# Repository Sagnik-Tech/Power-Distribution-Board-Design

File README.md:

Custom design of a Power Distribution Board from scratch which can provide different voltages required by the various subsystems of a Mars Rover

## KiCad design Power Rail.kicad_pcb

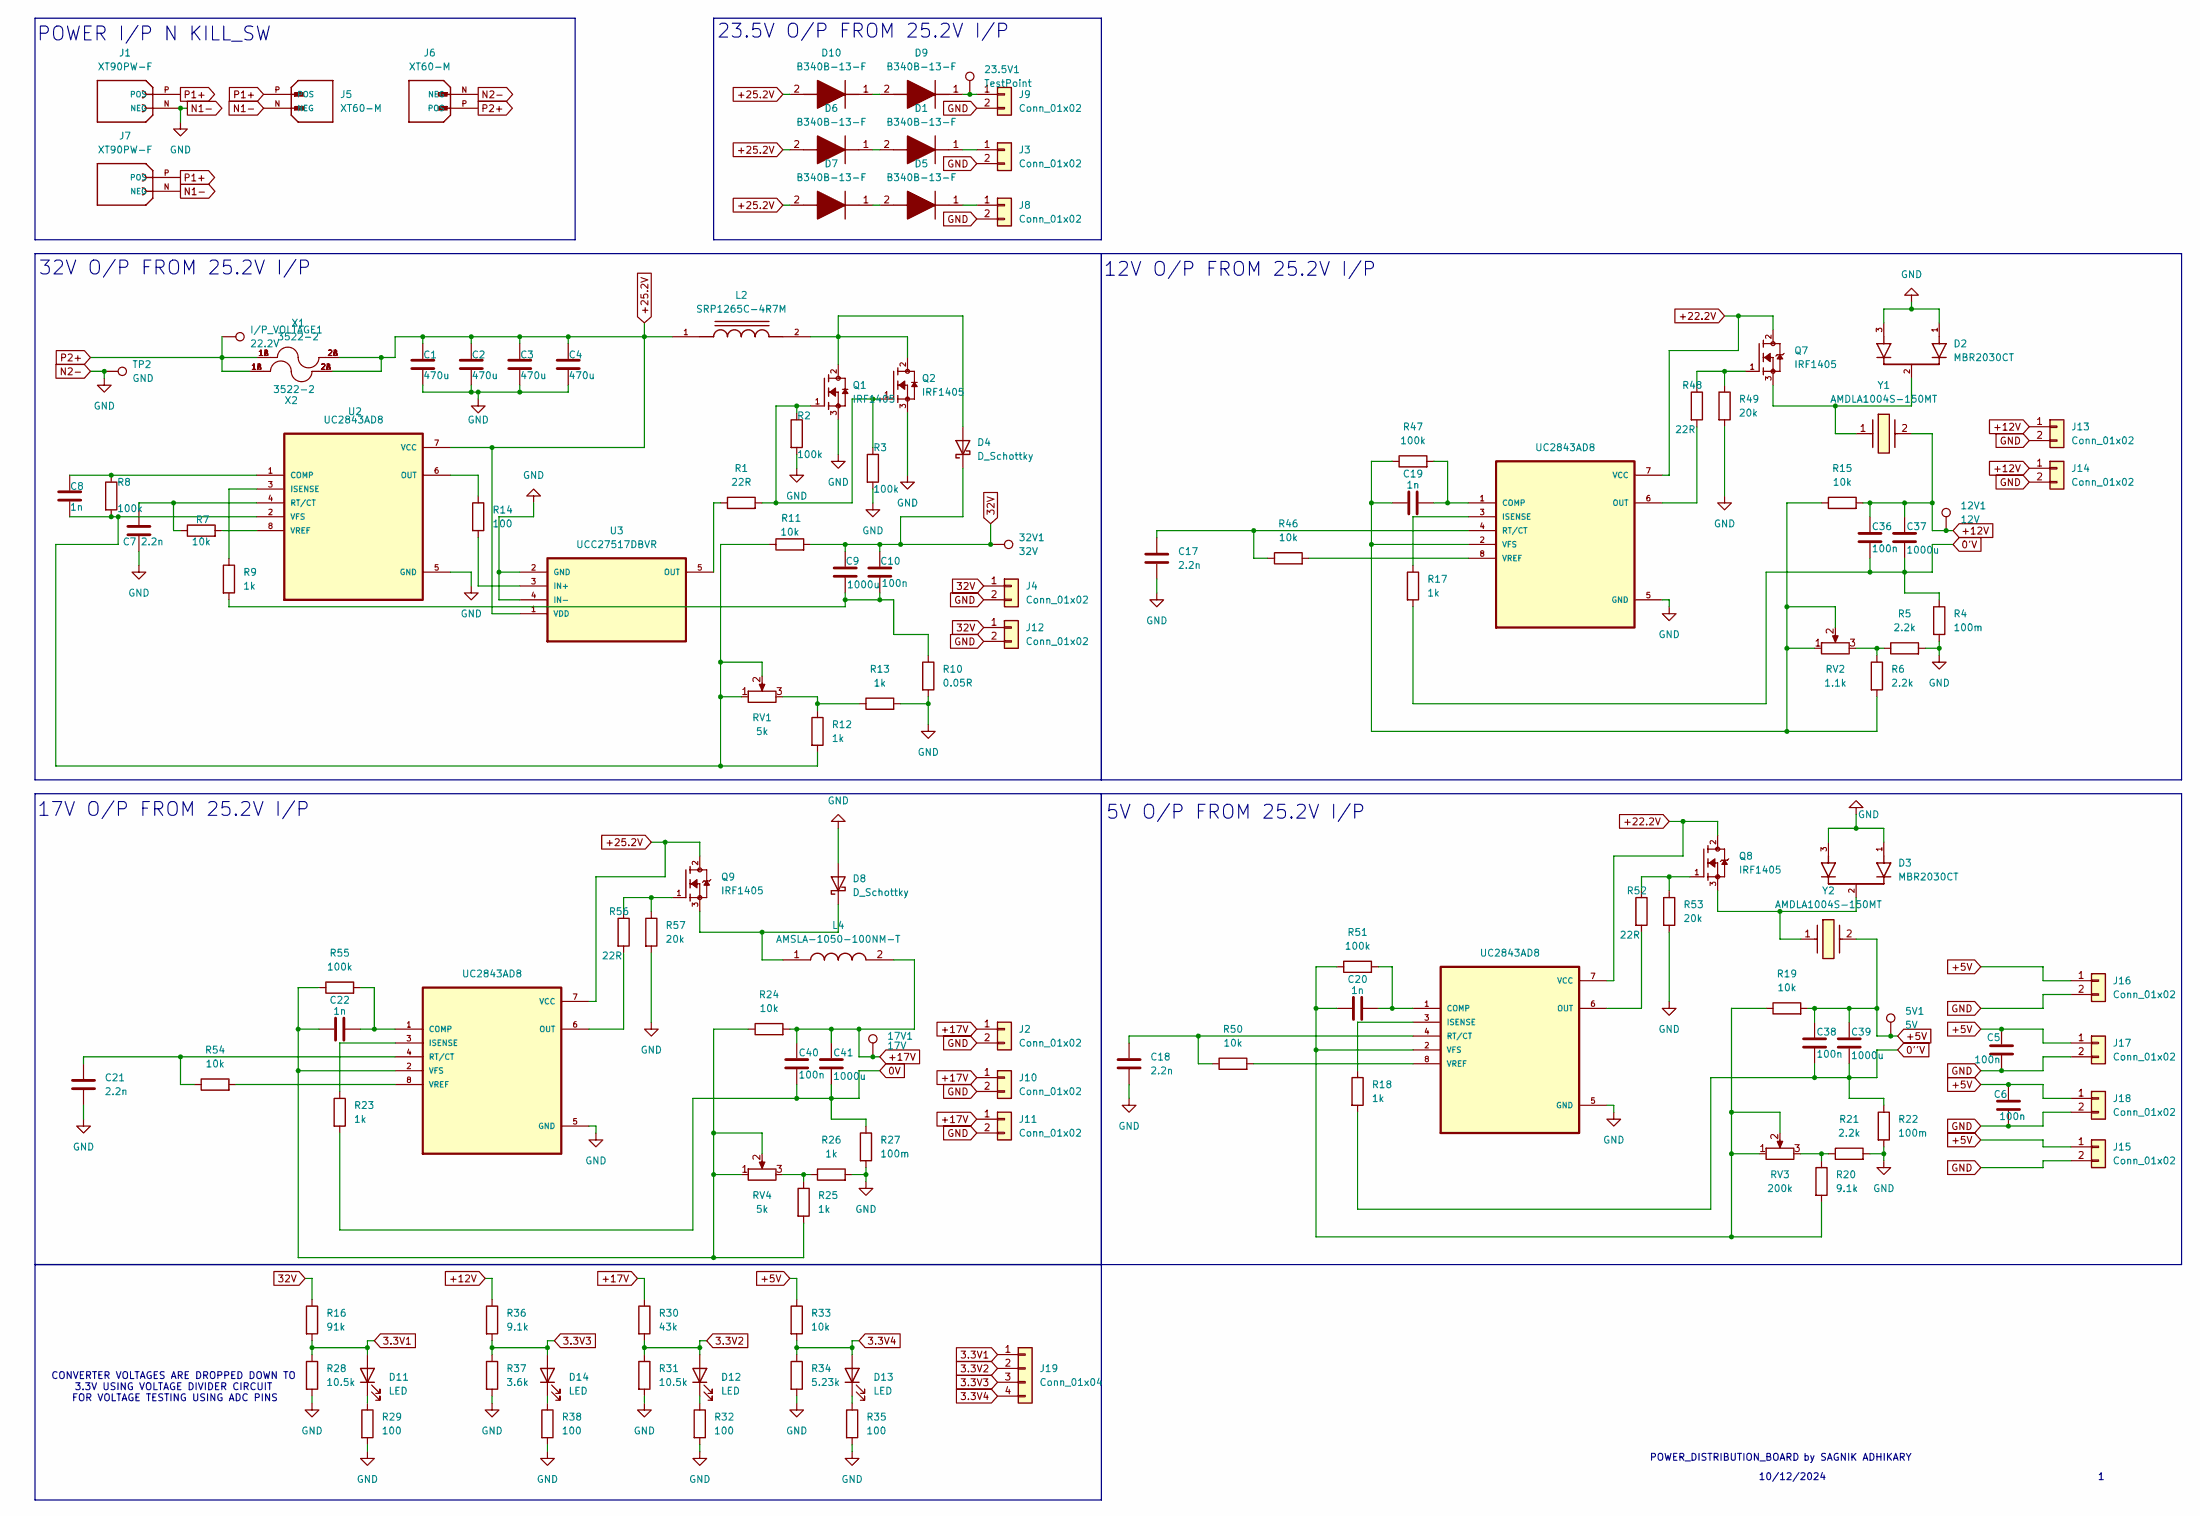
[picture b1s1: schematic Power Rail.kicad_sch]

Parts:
5V1: 5V; TestPoint_Pad_D2.0mm
12V1: 12V; TestPoint_Pad_D2.0mm
17V1: 17V; TestPoint_Pad_D2.0mm
23.5V1: TestPoint; TestPoint_Pad_D2.0mm
32V1: 32V; TestPoint_Pad_D2.0mm
C1, C2, C3, C4: 470u; C_Radial_D10.0mm_H20.0mm_P5.00mm
C5, C6, C10, C36, C38, C40: 100n; C_0805_2012Metric_Pad1.18x1.45mm_HandSolder
C7, C17, C18, C21: 2.2n; C_0805_2012Metric_Pad1.18x1.45mm_HandSolder
C8, C19, C20, C22: 1n; C_0805_2012Metric_Pad1.18x1.45mm_HandSolder
C9, C37, C39, C41: 1000u; C_Radial_D12.5mm_H20.0mm_P5.00mm
D1, D5, D6, D7, D9, D10: B340B-13-F; DIOM5336X250N; Mouser Part Number 621-B340B-F
D2, D3: MBR2030CT; TO-220-3_Vertical; PARTREV G2104
D4, D8: D_Schottky; TO1112P1562X470X2475-2
D11, D12, D13, D14: LED; LED_0805_2012Metric_Pad1.15x1.40mm_HandSolder
I/P_VOLTAGE1: 22.2V; TestPoint_Pad_D2.0mm
J1, J7: XT90PW-F; AMASS_XT90PW-F; PARTREV V00
J2, J3, J4, J8, J9, J10, J11, J12, J13, J14, J15, J16, J17, J18: Conn_01x02; PhoenixContact_GMSTBA_2,5_2-G-7,62_1x02_P7.62mm_Horizontal
J5, J6: XT60-M; AMASS_XT60-M; PARTREV V1.2
J19: Conn_01x04; JST_XH_B4B-XH-A_1x04_P2.50mm_Vertical
L2: SRP1265C-4R7M; IND_SRP1265C-4R7M; PARTREV 05/22
L4: AMSLA-1050-100NM-T; AMSLA1050100NMT; Manufacturer_Part_Number AMSLA-1050-100NM-T
Q1, Q2: IRF1405; TO254P1524X457-3N; PARTREV 2.2
Q7, Q8, Q9: IRF1405; TO254P1524X457-3N; PARTREV 09/21/10
R1, R48, R52, R56: 22R; R_0805_2012Metric_Pad1.20x1.40mm_HandSolder
R2, R3, R8, R47, R51, R55: 100k; R_0805_2012Metric_Pad1.20x1.40mm_HandSolder
R4, R22, R27: 100m; R_0805_2012Metric
R5, R6, R21: 2.2k; R_0805_2012Metric_Pad1.20x1.40mm_HandSolder
R7, R11, R15, R19, R24, R33, R46, R50, R54: 10k; R_0805_2012Metric_Pad1.20x1.40mm_HandSolder
R9, R12, R13, R17, R18, R23, R25, R26: 1k; R_0805_2012Metric_Pad1.20x1.40mm_HandSolder
R10: 0.05R; R_1206_3216Metric_Pad1.30x1.75mm_HandSolder
R14, R29, R32, R35, R38: 100; R_0805_2012Metric_Pad1.20x1.40mm_HandSolder
R16: 91k; R_0805_2012Metric_Pad1.20x1.40mm_HandSolder
R20, R36: 9.1k; R_0805_2012Metric_Pad1.20x1.40mm_HandSolder
R28, R31: 10.5k; R_0805_2012Metric_Pad1.20x1.40mm_HandSolder
R30: 43k; R_0805_2012Metric_Pad1.20x1.40mm_HandSolder
R34: 5.23k; R_0805_2012Metric_Pad1.20x1.40mm_HandSolder
R37: 3.6k; R_0805_2012Metric_Pad1.20x1.40mm_HandSolder
R49, R53, R57: 20k; R_0805_2012Metric_Pad1.20x1.40mm_HandSolder
RV1, RV4: 5k; Potentiometer_Bourns_3296W_Vertical
RV2: 1.1k; Potentiometer_Bourns_3296W_Vertical
RV3: 200k; Potentiometer_Bourns_3296W_Vertical
TP2: GND; TestPoint_Pad_D2.0mm
U2, U7, U8, U9: UC2843AD8; SOIC127P599X175-8N
U3: UCC27517DBVR; SOT95P280X145-5N
X1, X2: 3522-2; FUSE_3522-2; PARTREV J
Y1, Y2: AMDLA1004S-150MT; INDPM110100X400N; Mouser Part Number 815-AMDLA1004S-150MT

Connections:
0''V: C38.2, C39.2, R18.2, R22.1
0'V: C36.2, C37.2, R4.1, R17.2
0V: C40.2, C41.2, R23.2, R27.1
3.3V1: D11.2 (A), J19.1, R16.2, R28.1
3.3V2: D12.2 (A), J19.2, R30.2, R31.1
3.3V3: D14.2 (A), J19.3, R36.2, R37.1
3.3V4: D13.2 (A), J19.4, R33.2, R34.1
32V: 32V1.1, C9.1, C10.1, D4.1 (K), J4.1, J12.1, R11.2, R16.1
+5V: 5V1.1, C5.1, C6.1, C38.1, C39.1, J15.1, J16.1, J17.1, J18.1, R19.2, R33.1, Y2.2
+12V: 12V1.1, C36.1, C37.1, J13.1, J14.1, R15.2, R36.1, Y1.2
+17V: 17V1.1, C40.1, C41.1, J2.1, J10.1, J11.1, L4.2, R24.2, R30.1
GND: C1.2, C2.2, C3.2, C4.2, C5.2, C6.2, C7.2, C17.2, C18.2, C21.2, D2.1, D2.3, D3.1, D3.3, D8.2 (A), J1.N (NEG), J2.2, J3.2, J4.2, J5.N (NEG), J6.N (NEG), J7.N (NEG), J8.2, J9.2, J10.2, J11.2, J12.2, J13.2, J14.2, J15.2, J16.2, J17.2, J18.2, Q1.3, Q2.3, R2.2, R3.2, R4.2, R5.2, R10.2, R13.2, R21.2, R22.2, R26.2, R27.2, R28.2, R29.2, R31.2, R32.2, R34.2, R35.2, R37.2, R38.2, R49.2, R53.2, R57.2, TP2.1, U2.5 (GND), U3.2 (GND), U3.4 (IN-), U7.5 (GND), U8.5 (GND), U9.5 (GND)
unnamed: C9.2, C10.2, R9.2, R10.1
unnamed: D1.2 (A), D6.1 (K)
unnamed: D1.1 (K), J3.1
unnamed: D2.2, Q7.3, Y1.1
unnamed: D3.2, Q8.3, Y2.1
unnamed: D4.2 (A), L2.2, Q1.2, Q2.2
unnamed: D5.2 (A), D7.1 (K)
unnamed: D5.1 (K), J8.1
unnamed: D8.1 (K), L4.1, Q9.3
unnamed: 23.5V1.1, D9.1 (K), J9.1
unnamed: D9.2 (A), D10.1 (K)
unnamed: D11.1 (K), R29.1
unnamed: D12.1 (K), R32.1
unnamed: D13.1 (K), R35.1
unnamed: D14.1 (K), R38.1
unnamed: Q1.1, Q2.1, R1.2, R2.1, R3.1
unnamed: Q7.1, R48.1, R49.1
unnamed: Q8.1, R52.1, R53.1
unnamed: Q9.1, R56.1, R57.1
unnamed: R5.1, R6.1, RV2.3
unnamed: R12.1, R13.1, RV1.3
unnamed: R20.1, R21.1, RV3.3
unnamed: R25.1, R26.1, RV4.3
unnamed: C8.1, R8.1, U2.1 (COMP)
unnamed: R9.1, U2.3 (ISENSE)
unnamed: R14.1, U2.6 (OUT)
unnamed: C7.1, R7.1, U2.4 (RT/CT)
unnamed: C8.2, R8.2, R11.1, R12.2, RV1.1, RV1.2, U2.2 (VFS)
unnamed: R7.2, U2.8 (VREF)
unnamed: R14.2, U3.3 (IN+)
unnamed: R1.1, U3.5 (OUT)
unnamed: C19.2, R47.2, U7.1 (COMP)
unnamed: R17.1, U7.3 (ISENSE)
unnamed: R48.2, U7.6 (OUT)
unnamed: C17.1, R46.1, U7.4 (RT/CT)
unnamed: C19.1, R6.2, R15.1, R47.1, RV2.1, RV2.2, U7.2 (VFS)
unnamed: R46.2, U7.8 (VREF)
unnamed: C20.2, R51.2, U8.1 (COMP)
unnamed: R18.1, U8.3 (ISENSE)
unnamed: R52.2, U8.6 (OUT)
unnamed: C18.1, R50.1, U8.4 (RT/CT)
unnamed: C20.1, R19.1, R20.2, R51.1, RV3.1, RV3.2, U8.2 (VFS)
unnamed: R50.2, U8.8 (VREF)
unnamed: C22.2, R55.2, U9.1 (COMP)
unnamed: R23.1, U9.3 (ISENSE)
unnamed: R56.2, U9.6 (OUT)
unnamed: C21.1, R54.1, U9.4 (RT/CT)
unnamed: C22.1, R24.1, R25.2, R55.1, RV4.1, RV4.2, U9.2 (VFS)
unnamed: R54.2, U9.8 (VREF)
P1+: J1.P (POS), J5.P (POS), J7.P (POS)
P2+: I/P_VOLTAGE1.1, J6.P (POS), X1.1A, X1.1B, X2.1A, X2.1B

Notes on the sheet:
POWER_DISTRIBUTION_BOARD
FOR VOLTAGE TESTING USING ADC PINS
12V O/P FROM 25.2V I/P
5V O/P FROM 25.2V I/P
23.5V O/P FROM 25.2V I/P
10/12/2024
POWER I/P N KILL_SW
17V O/P FROM 25.2V I/P
CONVERTER VOLTAGES ARE DROPPED DOWN TO 3.3V USING VOLTAGE DIVIDER CIRCUIT
by SAGNIK ADHIKARY
32V O/P FROM 25.2V I/P

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
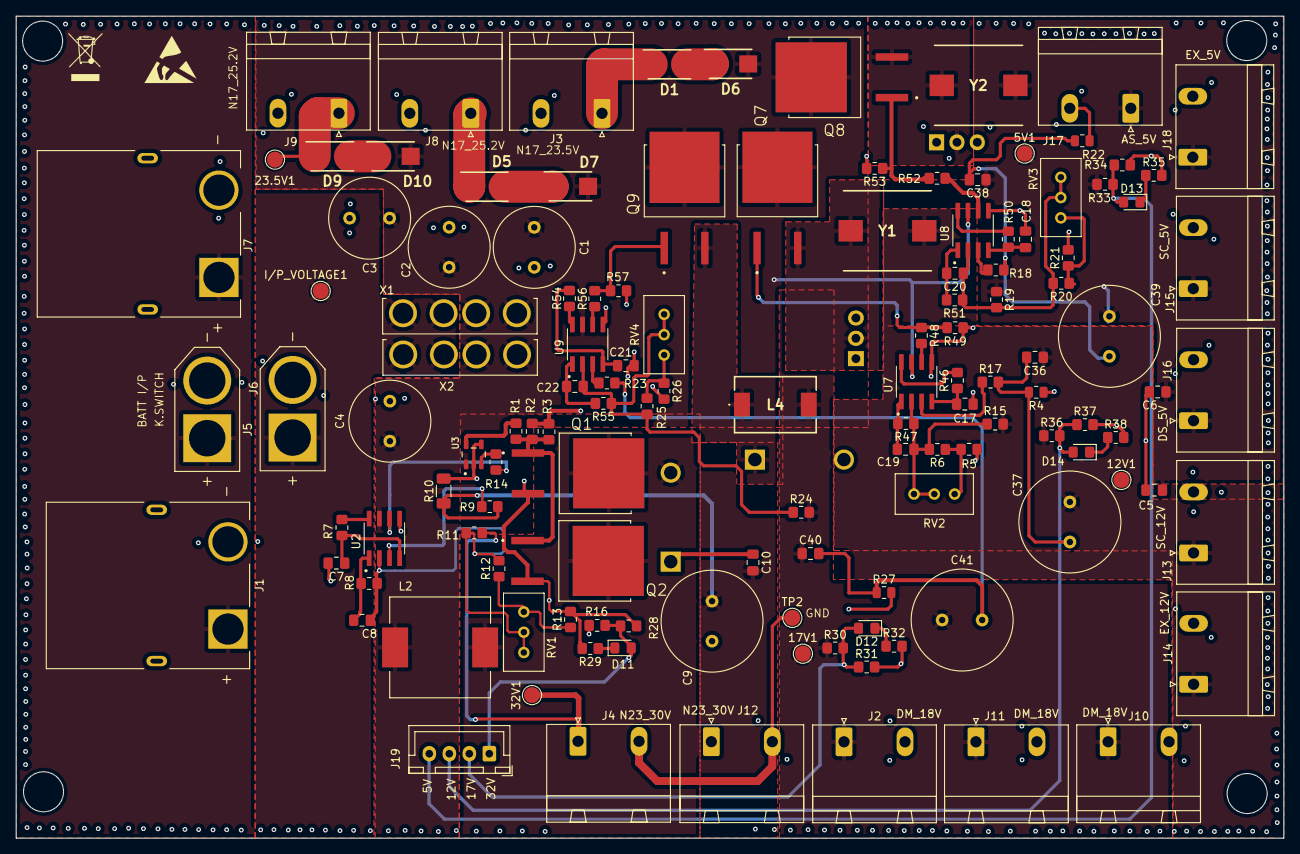
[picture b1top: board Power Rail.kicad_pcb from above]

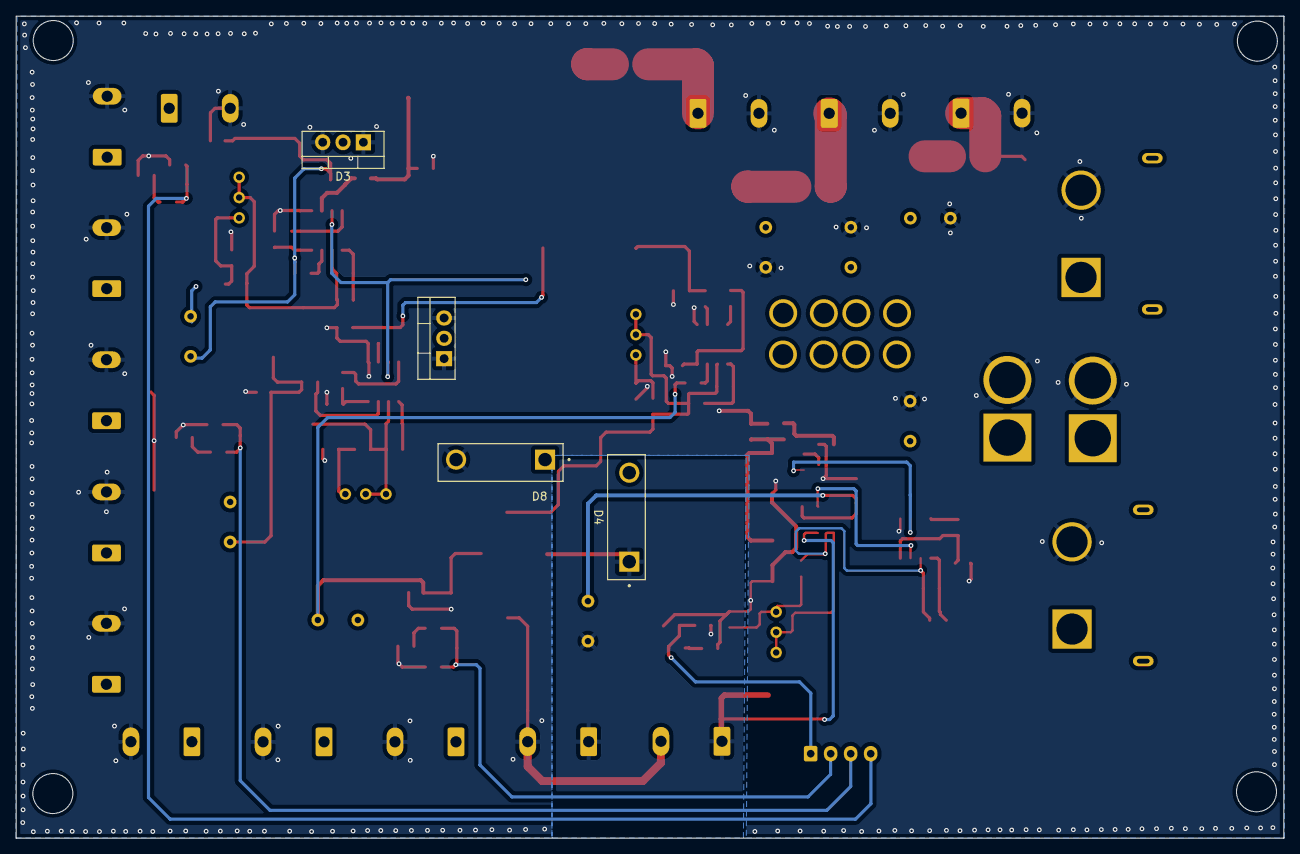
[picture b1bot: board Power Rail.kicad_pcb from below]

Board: 2 copper layers, 158.4 x 102.7 mm, 132 parts (4 on the bottom side), 64 nets.
